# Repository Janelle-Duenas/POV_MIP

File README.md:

# POV_MIP
This project was developed by the UCSD Coordinated Robotics Laboratory

These folders contain all the files for the educational POV Mechanism that is mounted on the MIP.
The SolidWorks files folder is separated into plastic parts, eletromechanical parts and hardware.
Please download all these contents as displayed on the repository to retain the parts references for the main assembly.
The PCB Eagle files folder contains the schematic/board files.
The Code folder contains C files that use TI-RTOS.

For a more detail description of this project please see the following document

AIAA Confrence paper : link TBD

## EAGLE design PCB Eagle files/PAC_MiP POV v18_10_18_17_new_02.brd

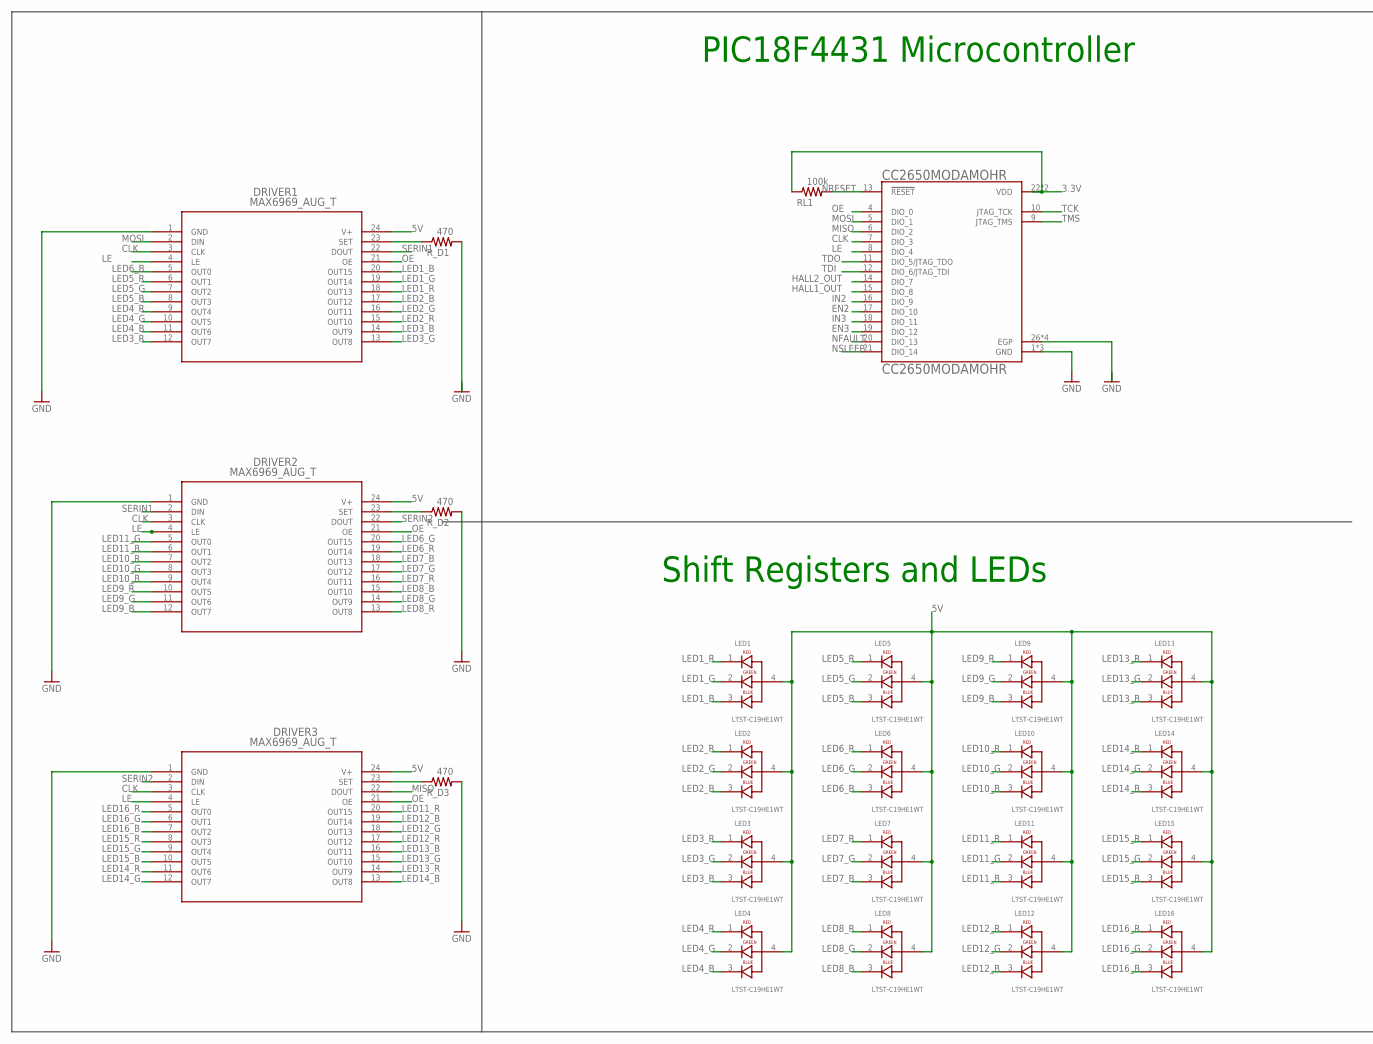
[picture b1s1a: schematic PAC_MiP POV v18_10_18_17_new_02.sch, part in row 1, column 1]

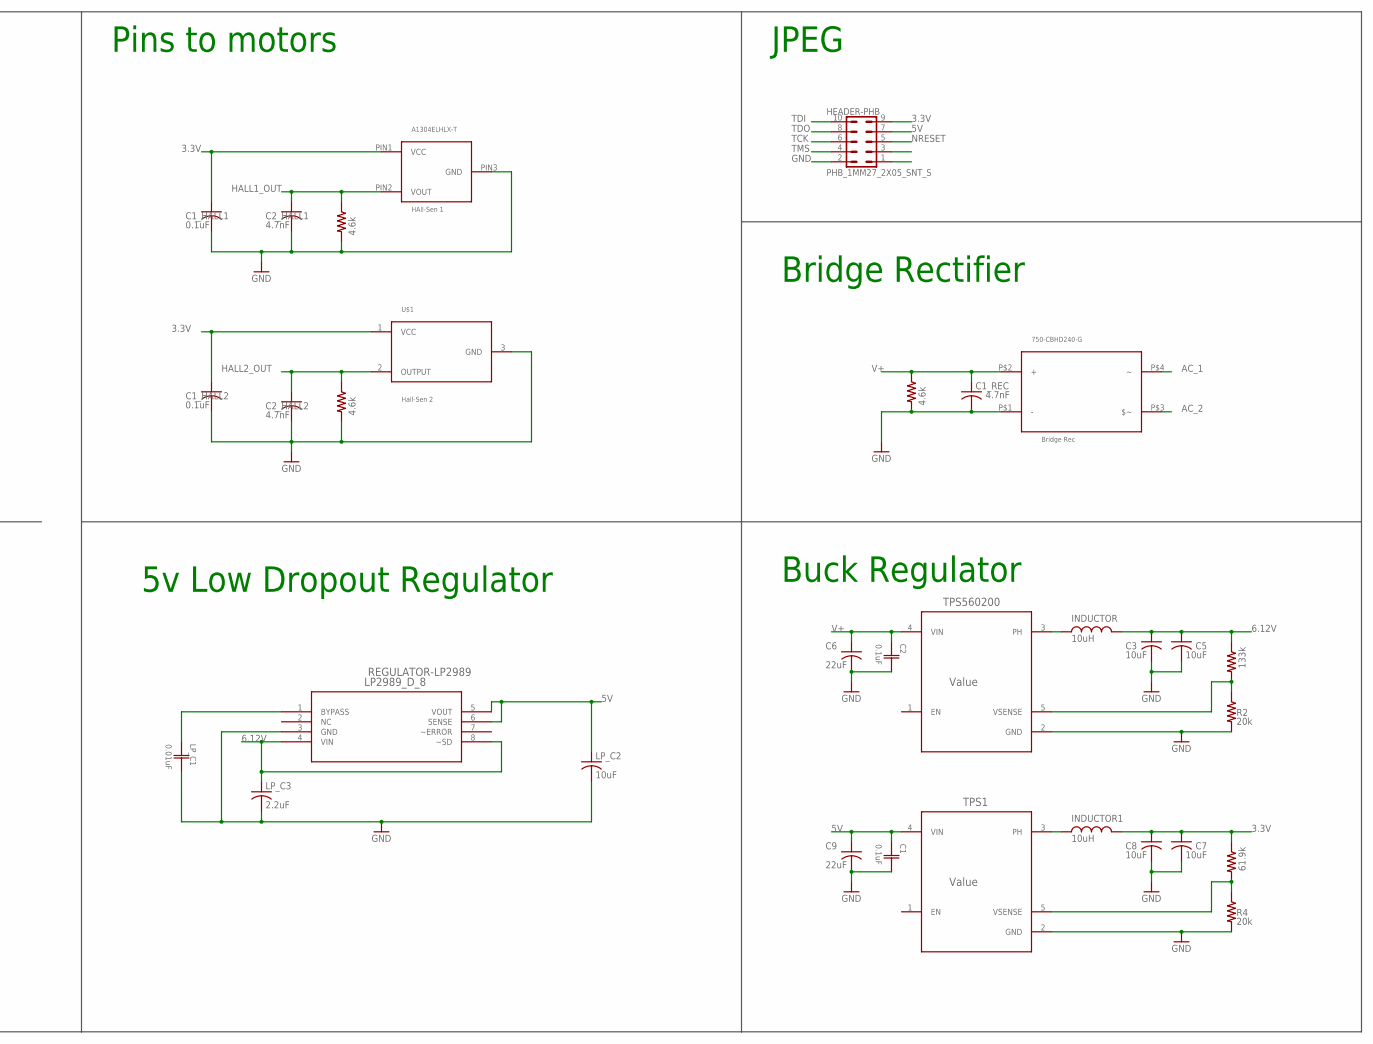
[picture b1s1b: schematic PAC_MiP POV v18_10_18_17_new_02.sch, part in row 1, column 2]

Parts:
750-CBHD240-G: Bridge Rec; 750-CDBHD240-G
A1304ELHLX-T: HAll-Sen 1; A1304ELHLX-T
C1, C2: 0.1uF; 0508
C1_HALL1, C1_HALL2: 0.1uF; C0805
C1_REC, C2_HALL1, C2_HALL2: 4.7nF; C0805
C3, C5, C7, C8: 10uF; C0805
C6, C9: 22uF; C0805
CC2650MODAMOHR: CC2650MODAMOHR; XCVR_CC2650MODAMOHR
DRIVER1, DRIVER2, DRIVER3: MAX6969_AUG_T; 21_0066J_24
HEADER-PHB: PHB_1MM27_2X05_SNT_S; PHB_1MM27_2X05_SNT
INDUCTOR, INDUCTOR1: 10uH; CDPH4D19FNP100MC
LED1, LED2, LED3, LED4, LED5, LED6, LED7, LED8, LED9, LED10, LED11, LED12, LED13, LED14, LED15, LED16: LTST-C19HE1WT; LEDSC85P160X160X35-4N
LP_C1: 0.01uF; LLL18
LP_C2: 10uF; C0805
LP_C3: 2.2uF; C0805
R1: 133k; R0805
R1_HALL, R1_HALL2, R1_REC: 4.6k; R0805
R2, R4: 20k; R0805
R3: 61.9k; R0805
REGULATOR-LP2989: LP2989_D_8; M08A; PARTNUMBER LP2989AIM-18
RL1: 100k; R0805
R_D1, R_D2, R_D3: 470; R0805
TPS1, TPS560200: Value; DBV0005A_N
U$1: Hall-Sen 2; SOT-23-3

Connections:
3.3V: A1304ELHLX-T.PIN1 (VCC), C1_HALL1.1, C1_HALL2.1, C7.1, C8.1, CC2650MODAMOHR.22 (VDD), CC2650MODAMOHR.23 (VDD), HEADER-PHB.9, INDUCTOR1.P$2, R3.1, RL1.1, U$1.1 (VCC)
5V: C1.1, C9.1, DRIVER1.24 (V+), DRIVER2.24 (V+), DRIVER3.24 (V+), HEADER-PHB.7, LED1.4, LED2.4, LED3.4, LED4.4, LED5.4, LED6.4, LED7.4, LED8.4, LED9.4, LED10.4, LED11.4, LED12.4, LED13.4, LED14.4, LED15.4, LED16.4, LP_C2.1, REGULATOR-LP2989.5 (VOUT), REGULATOR-LP2989.6 (SENSE), TPS1.4 (VIN)
6.12V: C3.1, C5.1, INDUCTOR.P$2, LP_C3.1, R1.1, REGULATOR-LP2989.4 (VIN), REGULATOR-LP2989.8 (~SD)
AC_1: 750-CBHD240-G.P$4
AC_2: 750-CBHD240-G.P$3 ($~)
CLK: CC2650MODAMOHR.7 (DIO_3), DRIVER1.3 (CLK), DRIVER2.3 (CLK), DRIVER3.3 (CLK)
EN2: CC2650MODAMOHR.17 (DIO_10)
EN3: CC2650MODAMOHR.19 (DIO_12)
GND: 750-CBHD240-G.P$1 (-), A1304ELHLX-T.PIN3 (GND), C1.2, C1_HALL1.2, C1_HALL2.2, C1_REC.2, C2.2, C2_HALL1.2, C2_HALL2.2, C3.2, C5.2, C6.2, C7.2, C8.2, C9.2, CC2650MODAMOHR.1 (GND), CC2650MODAMOHR.3 (GND), CC2650MODAMOHR.25 (GND), CC2650MODAMOHR.26 (EGP), CC2650MODAMOHR.27 (EGP), CC2650MODAMOHR.28 (EGP), CC2650MODAMOHR.29 (EGP), DRIVER1.1 (GND), DRIVER2.1 (GND), DRIVER3.1 (GND), HEADER-PHB.2, LP_C1.2, LP_C2.2, LP_C3.2, R1_HALL.2, R1_HALL2.2, R1_REC.2, R2.2, R4.2, REGULATOR-LP2989.3 (GND), R_D2.2, R_D3.2, TPS1.2 (GND), TPS560200.2 (GND), U$1.3 (GND)
HALL1_OUT: A1304ELHLX-T.PIN2 (VOUT), C2_HALL1.1, CC2650MODAMOHR.15 (DIO_8), R1_HALL.1
HALL2_OUT: C2_HALL2.1, CC2650MODAMOHR.14 (DIO_7), R1_HALL2.1, U$1.2 (OUTPUT)
IN2: CC2650MODAMOHR.16 (DIO_9)
IN3: CC2650MODAMOHR.18 (DIO_11)
LE: CC2650MODAMOHR.8 (DIO_4), DRIVER1.4 (LE), DRIVER2.4 (LE), DRIVER3.4 (LE)
LED1_B: DRIVER1.20 (OUT15), LED1.3
LED1_G: DRIVER1.19 (OUT14), LED1.2
LED1_R: DRIVER1.18 (OUT13), LED1.1
LED2_B: DRIVER1.17 (OUT12), LED2.3
LED2_G: DRIVER1.16 (OUT11), LED2.2
LED2_R: DRIVER1.15 (OUT10), LED2.1
LED3_B: DRIVER1.14 (OUT9), LED3.3
LED3_G: DRIVER1.13 (OUT8), LED3.2
LED3_R: DRIVER1.12 (OUT7), LED3.1
LED4_B: DRIVER1.11 (OUT6), LED4.3
LED4_G: DRIVER1.10 (OUT5), LED4.2
LED4_R: DRIVER1.9 (OUT4), LED4.1
LED5_B: DRIVER1.8 (OUT3), LED5.3
LED5_G: DRIVER1.7 (OUT2), LED5.2
LED5_R: DRIVER1.6 (OUT1), LED5.1
LED6_B: DRIVER1.5 (OUT0), LED6.3
LED6_G: DRIVER2.20 (OUT15), LED6.2
LED6_R: DRIVER2.19 (OUT14), LED6.1
LED7_B: DRIVER2.18 (OUT13), LED7.3
LED7_G: DRIVER2.17 (OUT12), LED7.2
LED7_R: DRIVER2.16 (OUT11), LED7.1
LED8_B: DRIVER2.15 (OUT10), LED8.3
LED8_G: DRIVER2.14 (OUT9), LED8.2
LED8_R: DRIVER2.13 (OUT8), LED8.1
LED9_B: DRIVER2.12 (OUT7), LED9.3
LED9_G: DRIVER2.11 (OUT6), LED9.2
LED9_R: DRIVER2.10 (OUT5), LED9.1
LED10_B: DRIVER2.9 (OUT4), LED10.3
LED10_G: DRIVER2.8 (OUT3), LED10.2
LED10_R: DRIVER2.7 (OUT2), LED10.1
LED11_B: DRIVER2.6 (OUT1), LED11.3
LED11_G: DRIVER2.5 (OUT0), LED11.2
LED11_R: DRIVER3.20 (OUT15), LED11.1
LED12_B: DRIVER3.19 (OUT14), LED12.3
LED12_G: DRIVER3.18 (OUT13), LED12.2
LED12_R: DRIVER3.17 (OUT12), LED12.1
LED13_B: DRIVER3.16 (OUT11), LED13.3
LED13_G: DRIVER3.15 (OUT10), LED13.2
LED13_R: DRIVER3.14 (OUT9), LED13.1
LED14_B: DRIVER3.13 (OUT8), LED14.3
LED14_G: DRIVER3.12 (OUT7), LED14.2
LED14_R: DRIVER3.11 (OUT6), LED14.1
LED15_B: DRIVER3.10 (OUT5), LED15.3
LED15_G: DRIVER3.9 (OUT4), LED15.2
LED15_R: DRIVER3.8 (OUT3), LED15.1
LED16_B: DRIVER3.7 (OUT2), LED16.3
LED16_G: DRIVER3.6 (OUT1), LED16.2
LED16_R: DRIVER3.5 (OUT0), LED16.1
MISO: CC2650MODAMOHR.6 (DIO_2), DRIVER3.22 (DOUT)
MOSI: CC2650MODAMOHR.5 (DIO_1), DRIVER1.2 (DIN)
unnamed: INDUCTOR.P$1, TPS560200.3 (PH)
unnamed: DRIVER3.23 (SET), R_D3.1
unnamed: R1.2, R2.1, TPS560200.5 (VSENSE)
unnamed: R3.2, R4.1, TPS1.5 (VSENSE)
unnamed: INDUCTOR1.P$1, TPS1.3 (PH)
unnamed: DRIVER2.23 (SET), R_D2.1
unnamed: DRIVER1.23 (SET), R_D1.1
unnamed: LP_C1.1, REGULATOR-LP2989.1 (BYPASS)
NFAULT: CC2650MODAMOHR.20 (DIO_13)
NRESET: CC2650MODAMOHR.13 (!RESET), HEADER-PHB.5, RL1.2
NSLEEP: CC2650MODAMOHR.21 (DIO_14)
OE: CC2650MODAMOHR.4 (DIO_0), DRIVER1.21 (OE), DRIVER2.21 (OE), DRIVER3.21 (OE)
SERIN1: DRIVER1.22 (DOUT), DRIVER2.2 (DIN)
SERIN2: DRIVER2.22 (DOUT), DRIVER3.2 (DIN)
TCK: CC2650MODAMOHR.10 (JTAG_TCK), HEADER-PHB.6
TDI: CC2650MODAMOHR.12 (DIO_6/JTAG_TDI), HEADER-PHB.10
TDO: CC2650MODAMOHR.11 (DIO_5/JTAG_TDO), HEADER-PHB.8
TMS: CC2650MODAMOHR.9 (JTAG_TMS), HEADER-PHB.4
V+: 750-CBHD240-G.P$2 (+), C1_REC.1, C2.1, C6.1, R1_REC.1, TPS560200.4 (VIN)

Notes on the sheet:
Pins to motors
Buck Regulator
Bridge Rectifier
PIC18F4431 Microcontroller
JPEG
Shift Registers and LEDs
5v Low Dropout Regulator

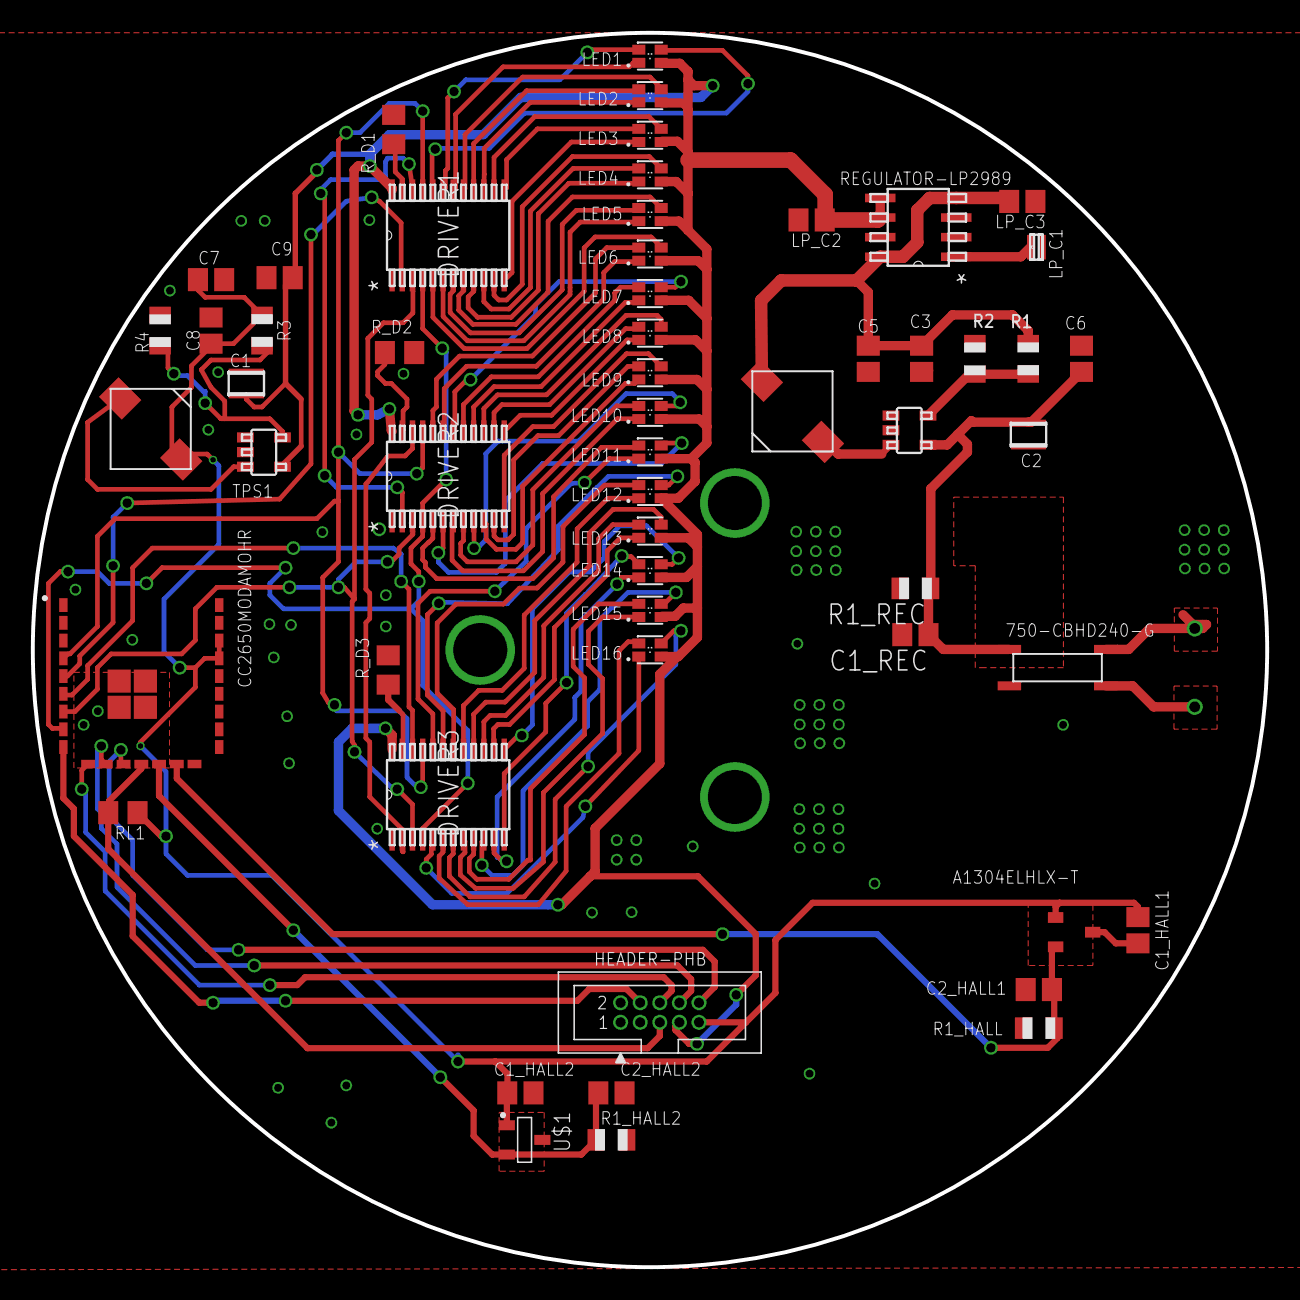
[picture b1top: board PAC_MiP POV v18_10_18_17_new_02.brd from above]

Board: 4 copper layers, 80.0 x 80.0 mm, 56 parts (0 on the bottom side), 75 nets.

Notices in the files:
parts and their libraries:
COPYRIGHT: Copyright (C) 2015 Accelerated Designs. All rights reserved
